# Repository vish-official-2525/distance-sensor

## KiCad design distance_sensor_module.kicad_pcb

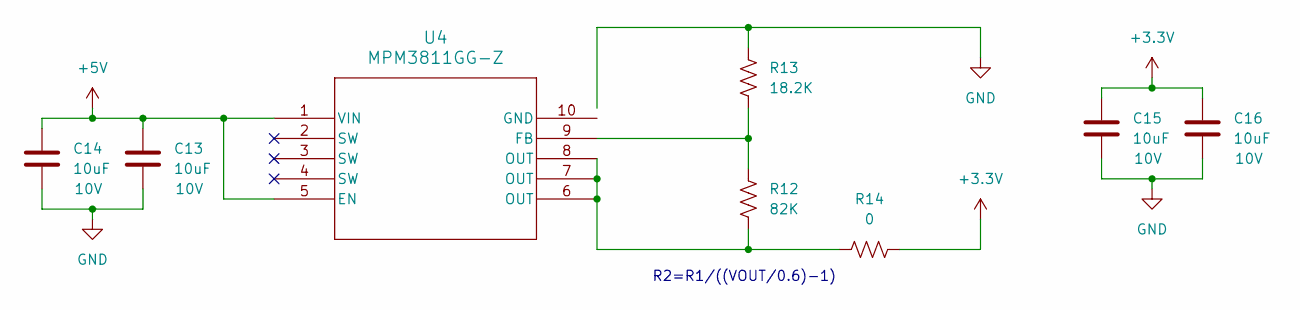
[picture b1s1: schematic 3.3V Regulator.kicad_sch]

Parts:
C13, C14, C15, C16: 10uF; C_0402_1005Metric_Pad0.74x0.62mm_HandSolder
R12: 82K; R_0402_1005Metric_Pad0.72x0.64mm_HandSolder
R13: 18.2K; R_0402_1005Metric_Pad0.72x0.64mm_HandSolder
R14: 0; R_0402_1005Metric_Pad0.72x0.64mm_HandSolder
U4: MPM3811GG-Z; QFN2x2x1p6_MPM3811_MNP

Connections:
+3.3V: C15.1, C16.1, R14.2; also elsewhere on the board
GND: C13.2, C14.2, C15.2, C16.2, R13.1; also elsewhere on the board
unnamed: R12.2, R14.1, U4.6 (OUT), U4.7 (OUT), U4.8 (OUT)
unnamed: R12.1, R13.2, U4.9 (FB)
VDDL: C13.1, C14.1, U4.1 (VIN), U4.5 (EN); also elsewhere on the board

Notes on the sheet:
R2=R1/((VOUT/0.6)-1)

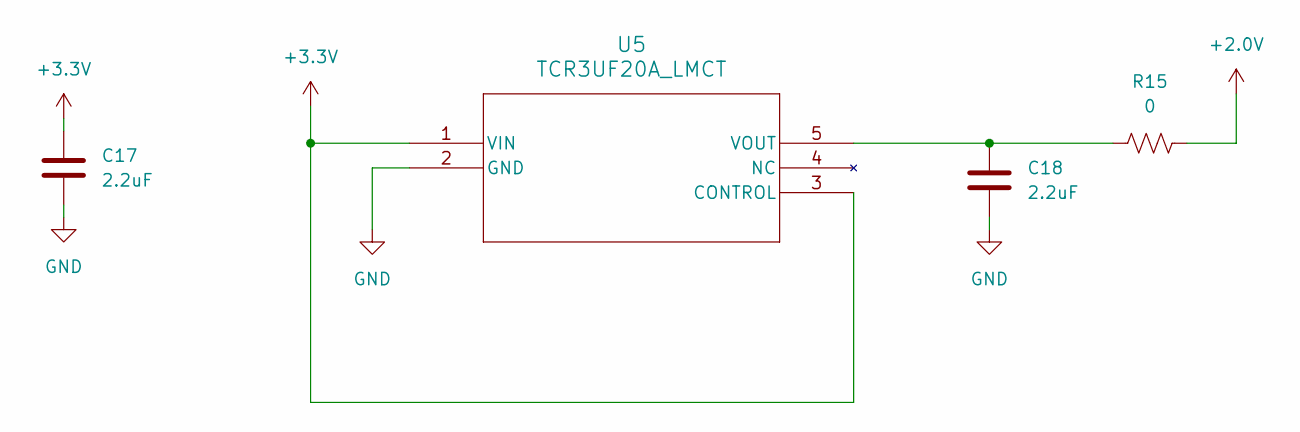
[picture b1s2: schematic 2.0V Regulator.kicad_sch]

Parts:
C17, C18: 2.2uF; C_0402_1005Metric_Pad0.74x0.62mm_HandSolder
R15: 0; R_0402_1005Metric_Pad0.72x0.64mm_HandSolder
U5: TCR3UF20A_LMCT; QFN2x2x1p6_MPM3811_MNP

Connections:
+2.0V: R15.2; also elsewhere on the board
+3.3V: C17.1, U5.1 (VIN), U5.3 (CONTROL); also elsewhere on the board
GND: C17.2, C18.2, U5.2 (GND); also elsewhere on the board
unnamed: C18.1, R15.1, U5.5 (VOUT)

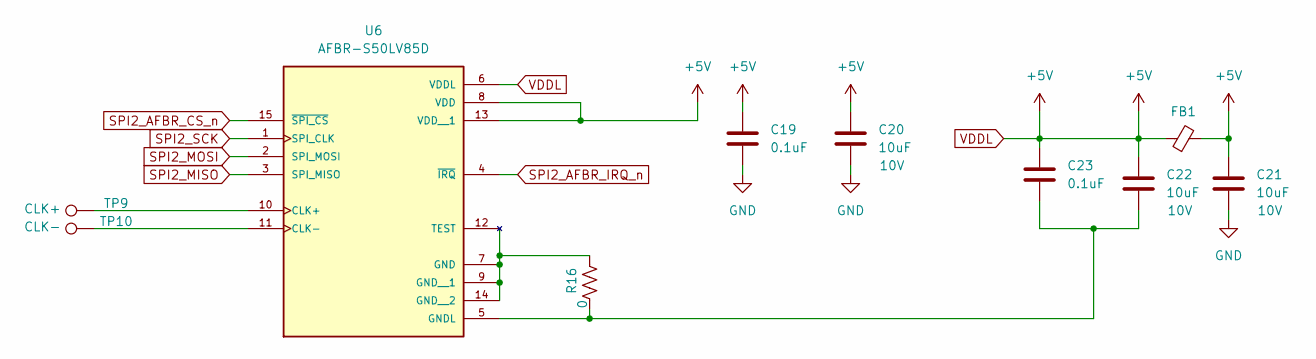
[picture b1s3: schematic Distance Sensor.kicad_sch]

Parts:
C19, C23: 0.1uF; C_0402_1005Metric_Pad0.74x0.62mm_HandSolder
C20, C21, C22: 10uF; C_0402_1005Metric_Pad0.74x0.62mm_HandSolder
FB1: FerriteBead_Small; L_0402_1005Metric_Pad0.77x0.64mm_HandSolder
R16: 0; R_0402_1005Metric_Pad0.72x0.64mm_HandSolder
TP9: CLK+; TestPoint_Pad_D1.0mm
TP10: CLK-; TestPoint_Pad_D1.0mm
U6: AFBR-S50LV85D; XCVR_AFBR-S50LV85D; PARTREV September 17, 2020

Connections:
GND: C19.2, C20.2, C21.2; also elsewhere on the board
unnamed: TP9.1, U6.10 (CLK+)
unnamed: TP10.1, U6.11 (CLK-)
unnamed: R16.2, U6.7 (GND), U6.9 (GND__1), U6.12 (TEST), U6.14 (GND__2)
unnamed: C22.2, C23.2, R16.1, U6.5 (GNDL)
SPI2_AFBR_CS_n: U6.15 (~SPI_CS); also elsewhere on the board
SPI2_AFBR_IRQ_n: U6.4 (~IRQ); also elsewhere on the board
SPI2_MISO: U6.3 (SPI_MISO); also elsewhere on the board
SPI2_MOSI: U6.2 (SPI_MOSI); also elsewhere on the board
SPI2_SCK: U6.1 (SPI_CLK); also elsewhere on the board
VDDL: C19.1, C20.1, C21.1, C22.1, C23.1, FB1.1, FB1.2, U6.6 (VDDL), U6.8 (VDD), U6.13 (VDD__1); also elsewhere on the board

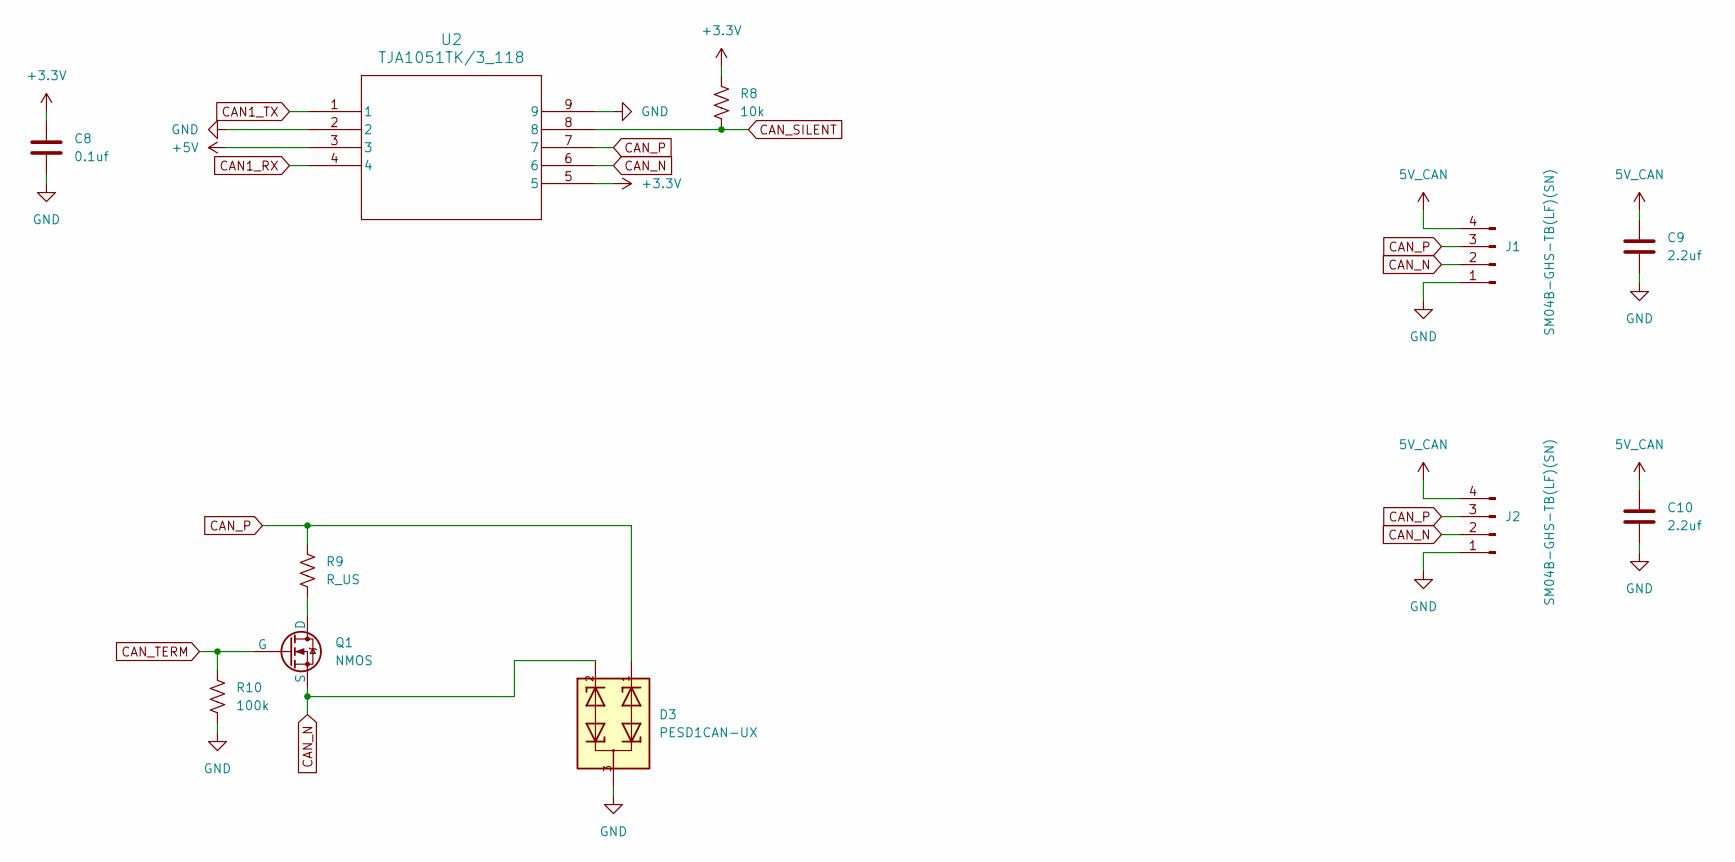
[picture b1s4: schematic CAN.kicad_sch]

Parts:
C8: 0.1uf; C_0402_1005Metric_Pad0.74x0.62mm_HandSolder
C9, C10: 2.2uf; C_0402_1005Metric_Pad0.74x0.62mm_HandSolder
D3: PESD1CAN-UX; SOT65P210X110-3N
J1, J2: SM04B-GHS-TB(LF)(SN); JST_GH_SM04B-GHS-TB_1x04-1MP_P1.25mm_Horizontal
Q1: NMOS; SOT91P240X110-3N
R8: 10k; R_0402_1005Metric_Pad0.72x0.64mm_HandSolder
R9: R_US; R_0402_1005Metric_Pad0.72x0.64mm_HandSolder
R10: 100k; R_0402_1005Metric_Pad0.72x0.64mm_HandSolder
U2: TJA1051TK/3_118; HVSON08_3X3_NXP

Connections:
5V_CAN: C9.1, C10.1, J1.4, J2.4; also elsewhere on the board
+3.3V: C8.1, R8.2, U2.5; also elsewhere on the board
CAN1_RX: U2.4; also elsewhere on the board
CAN1_TX: U2.1; also elsewhere on the board
CAN_N: D3.2, J1.2, J2.2, Q1.3 (S), U2.6
CAN_P: D3.1, J1.3, J2.3, R9.1, U2.7
CAN_SILENT: R8.1, U2.8; also elsewhere on the board
CAN_TERM: Q1.2 (G), R10.2; also elsewhere on the board
GND: C8.2, C9.2, C10.2, D3.3, J1.1, J2.1, R10.1, U2.2, U2.9; also elsewhere on the board
unnamed: Q1.1 (D), R9.2
VDDL: U2.3; also elsewhere on the board

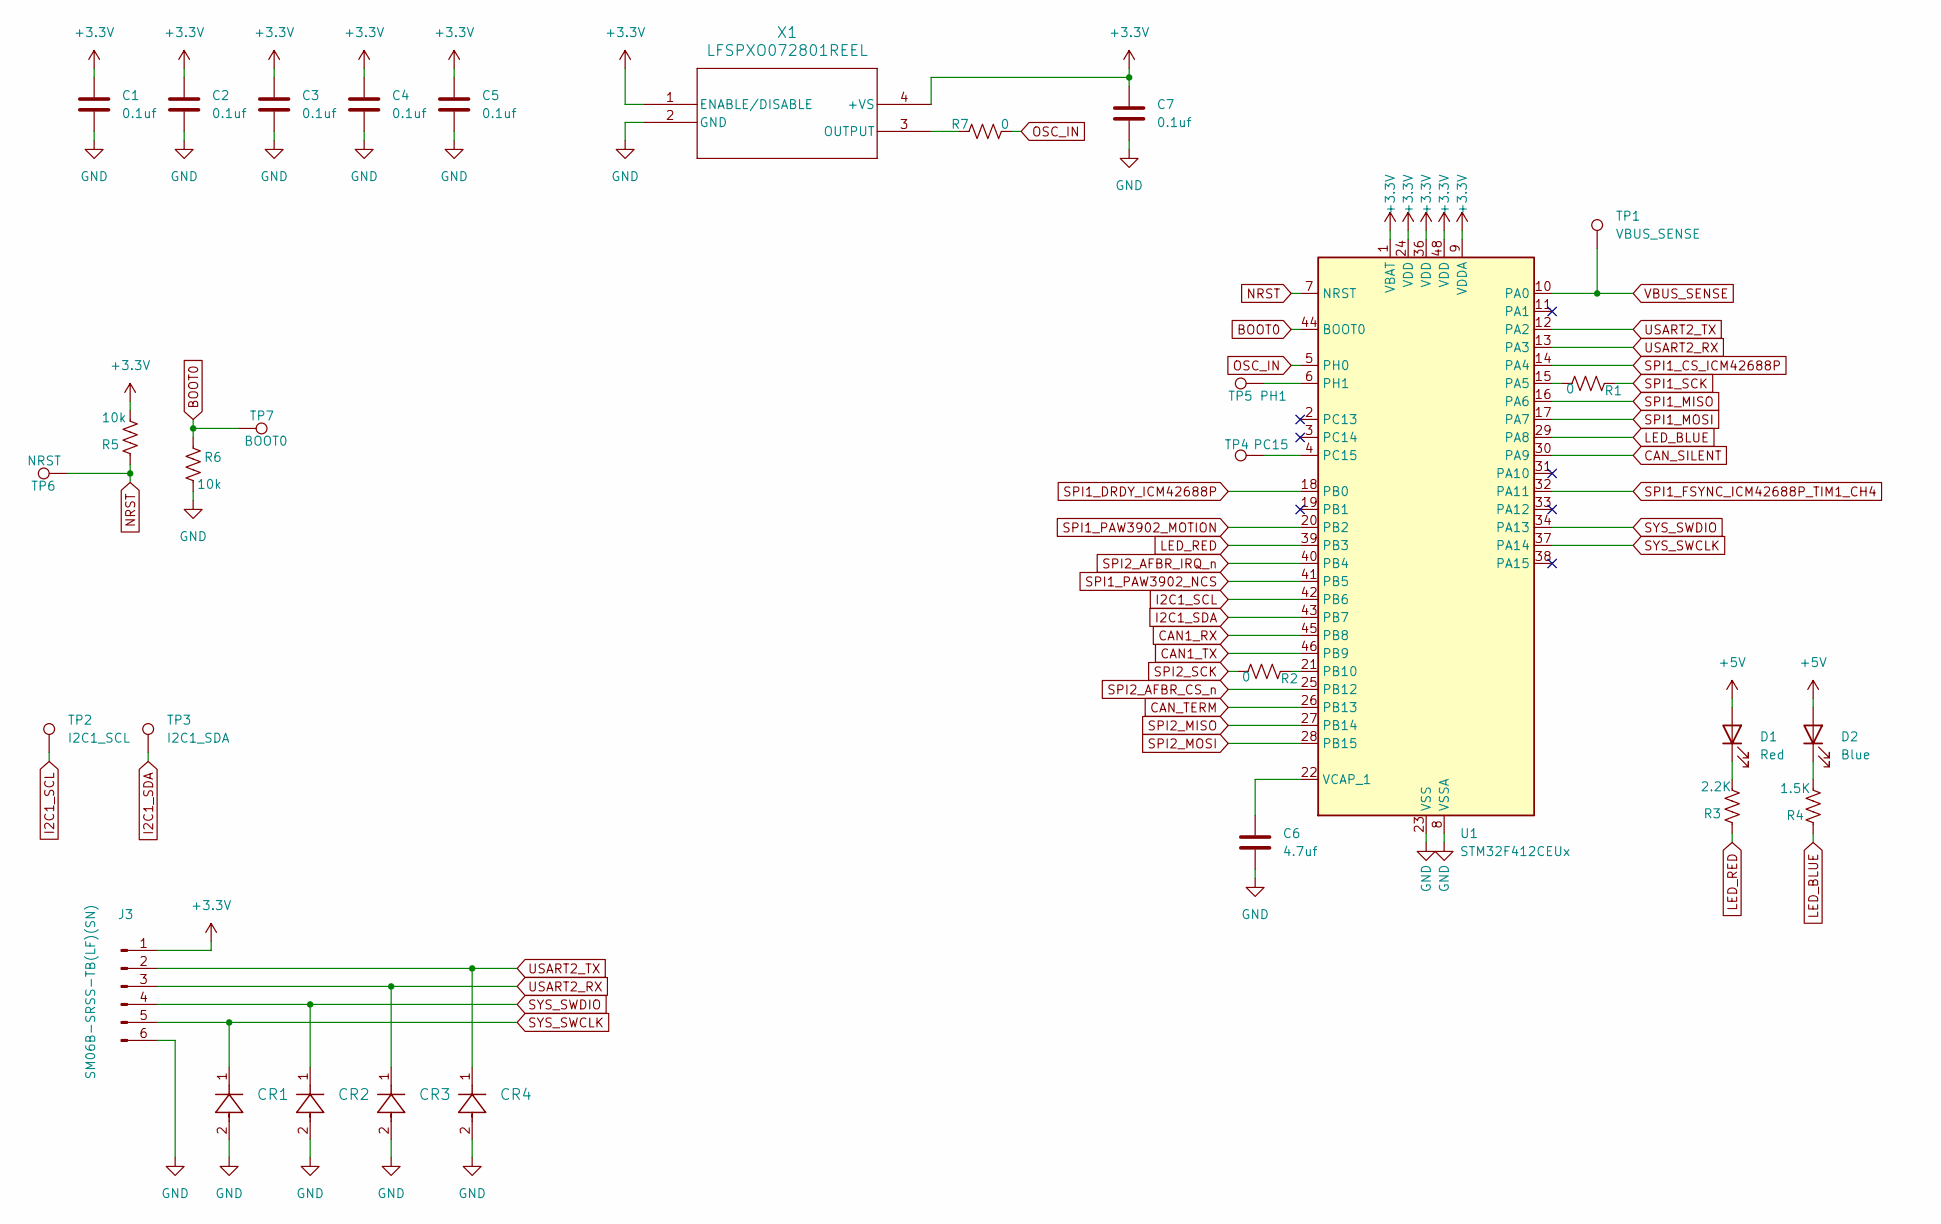
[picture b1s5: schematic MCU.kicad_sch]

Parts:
C1, C2, C3, C4, C5, C7: 0.1uf; C_0402_1005Metric_Pad0.74x0.62mm_HandSolder
C6: 4.7uf; C_0402_1005Metric_Pad0.74x0.62mm_HandSolder
CR1, CR2, CR3, CR4: ESD9C3.3ST5G; CR_ESD9C3.3ST5G_ONS
D1: Red; LED_0402_1005Metric_Pad0.77x0.64mm_HandSolder
D2: Blue; LED_0402_1005Metric_Pad0.77x0.64mm_HandSolder
J3: SM06B-SRSS-TB(LF)(SN); JST_SH_SM06B-SRSS-TB_1x06-1MP_P1.00mm_Horizontal
R1, R2, R7: 0; R_0402_1005Metric_Pad0.72x0.64mm_HandSolder
R3: 2.2K; R_0402_1005Metric_Pad0.72x0.64mm_HandSolder
R4: 1.5K; R_0402_1005Metric_Pad0.72x0.64mm_HandSolder
R5, R6: 10k; R_0402_1005Metric_Pad0.72x0.64mm_HandSolder
TP1: VBUS_SENSE; TestPoint_Pad_D1.0mm
TP2: I2C1_SCL; TestPoint_Pad_D1.0mm
TP3: I2C1_SDA; TestPoint_Pad_D1.0mm
TP4: PC15; TestPoint_Pad_D1.0mm
TP5: PH1; TestPoint_Pad_D1.0mm
TP6: NRST; TestPoint_Pad_D1.0mm
TP7: BOOT0; TestPoint_Pad_D1.0mm
U1: STM32F412CEUx; QFN-48-1EP_7x7mm_P0.5mm_EP3.5x3.5mm_ThermalVias
X1: LFSPXO072801REEL; LFSPXO072801REEL_IQD

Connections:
+3.3V: C1.1, C2.1, C3.1, C4.1, C5.1, C7.1, J3.1, R5.2, U1.1 (VBAT), U1.9 (VDDA), U1.24 (VDD), U1.36 (VDD), U1.48 (VDD), X1.1 (ENABLE/DISABLE), X1.4 (+VS); also elsewhere on the board
BOOT0: R6.1, TP7.1, U1.44 (BOOT0)
CAN1_RX: U1.45 (PB8); also elsewhere on the board
CAN1_TX: U1.46 (PB9); also elsewhere on the board
CAN_SILENT: U1.30 (PA9); also elsewhere on the board
CAN_TERM: U1.26 (PB13); also elsewhere on the board
GND: C1.2, C2.2, C3.2, C4.2, C5.2, C6.2, C7.2, CR1.2, CR2.2, CR3.2, CR4.2, J3.6, R6.2, U1.8 (VSSA), U1.23 (VSS), U1.35 (VSS), U1.47 (VSS), U1.49 (VSS), X1.2 (GND); also elsewhere on the board
I2C1_SCL: TP2.1, U1.42 (PB6)
I2C1_SDA: TP3.1, U1.43 (PB7)
LED_BLUE: R4.1, U1.29 (PA8)
LED_RED: R3.1, U1.39 (PB3)
NRST: R5.1, TP6.1, U1.7 (NRST)
unnamed: D1.1 (K), R3.2
unnamed: D2.1 (K), R4.2
unnamed: R1.1, U1.15 (PA5)
unnamed: R2.2, U1.21 (PB10)
unnamed: TP4.1, U1.4 (PC15)
unnamed: TP5.1, U1.6 (PH1)
unnamed: C6.1, U1.22 (VCAP_1)
unnamed: R7.1, X1.3 (OUTPUT)
OSC_IN: R7.2, U1.5 (PH0)
SPI1_CS_ICM42688P: U1.14 (PA4); also elsewhere on the board
SPI1_DRDY_ICM42688P: U1.18 (PB0); also elsewhere on the board
SPI1_FSYNC_ICM42688P_TIM1_CH4: U1.32 (PA11); also elsewhere on the board
SPI1_MISO: U1.16 (PA6); also elsewhere on the board
SPI1_MOSI: U1.17 (PA7); also elsewhere on the board
SPI1_PAW3902_MOTION: U1.20 (PB2); also elsewhere on the board
SPI1_PAW3902_NCS: U1.41 (PB5); also elsewhere on the board
SPI1_SCK: R1.2; also elsewhere on the board
SPI2_AFBR_CS_n: U1.25 (PB12); also elsewhere on the board
SPI2_AFBR_IRQ_n: U1.40 (PB4); also elsewhere on the board
SPI2_MISO: U1.27 (PB14); also elsewhere on the board
SPI2_MOSI: U1.28 (PB15); also elsewhere on the board
SPI2_SCK: R2.1; also elsewhere on the board
SYS_SWCLK: CR1.1, J3.5, U1.37 (PA14)
SYS_SWDIO: CR2.1, J3.4, U1.34 (PA13)
USART2_RX: CR3.1, J3.3, U1.13 (PA3)
USART2_TX: CR4.1, J3.2, U1.12 (PA2)
VBUS_SENSE: TP1.1, U1.10 (PA0)
VDDL: D1.2 (A), D2.2 (A); also elsewhere on the board

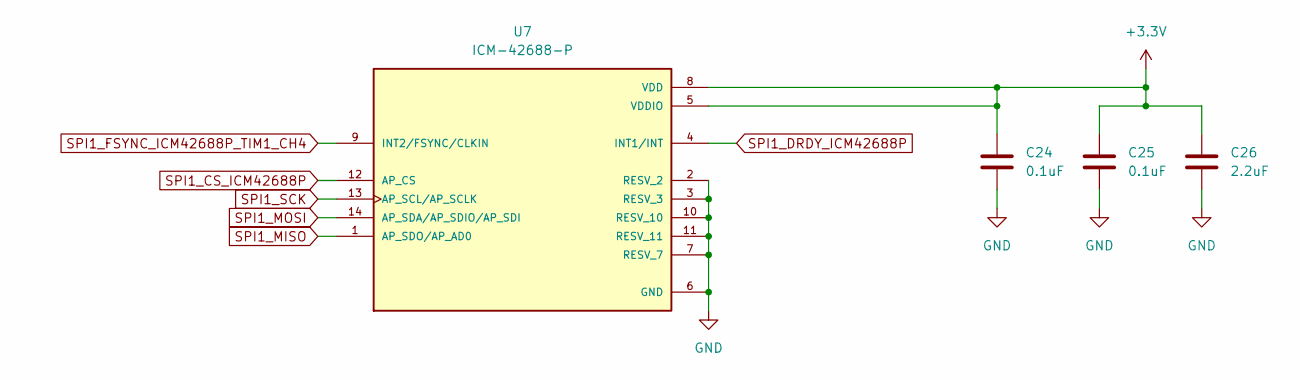
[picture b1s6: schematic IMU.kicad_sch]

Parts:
C24, C25: 0.1uF; C_0402_1005Metric_Pad0.74x0.62mm_HandSolder
C26: 2.2uF; C_0402_1005Metric_Pad0.74x0.62mm_HandSolder
U7: ICM-42688-P; PQFN50P300X250X97-14N; PARTREV 1.2

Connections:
+3.3V: C24.1, C25.1, C26.1, U7.5 (VDDIO), U7.8 (VDD); also elsewhere on the board
GND: C24.2, C25.2, C26.2, U7.2 (RESV_2), U7.3 (RESV_3), U7.6 (GND), U7.7 (RESV_7), U7.10 (RESV_10), U7.11 (RESV_11); also elsewhere on the board
SPI1_CS_ICM42688P: U7.12 (AP_CS); also elsewhere on the board
SPI1_DRDY_ICM42688P: U7.4 (INT1/INT); also elsewhere on the board
SPI1_FSYNC_ICM42688P_TIM1_CH4: U7.9 (INT2/FSYNC/CLKIN); also elsewhere on the board
SPI1_MISO: U7.1 (AP_SDO/AP_AD0); also elsewhere on the board
SPI1_MOSI: U7.14 (AP_SDA/AP_SDIO/AP_SDI); also elsewhere on the board
SPI1_SCK: U7.13 (AP_SCL/AP_SCLK); also elsewhere on the board

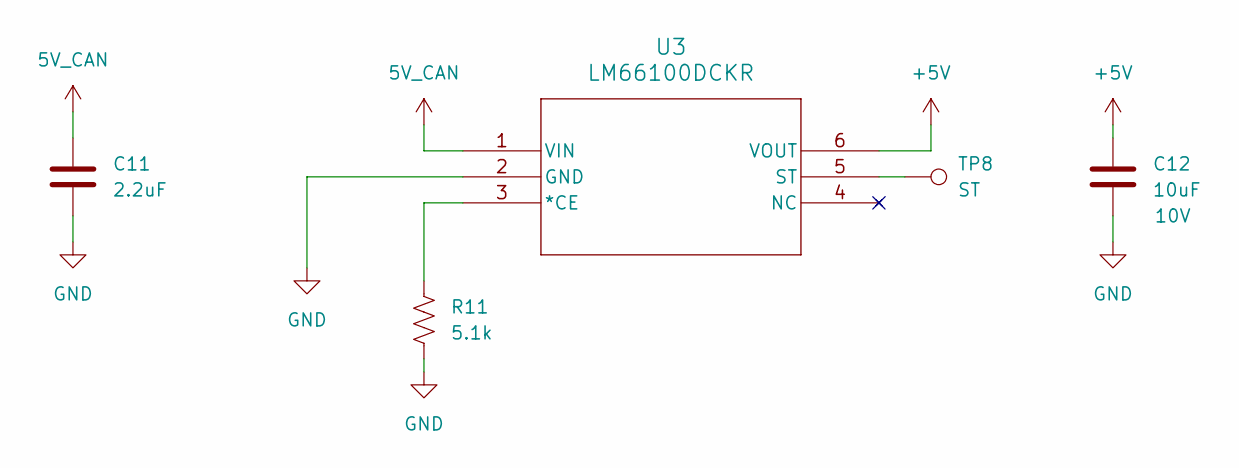
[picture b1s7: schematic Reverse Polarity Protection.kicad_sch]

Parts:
C11: 2.2uF; C_0402_1005Metric_Pad0.74x0.62mm_HandSolder
C12: 10uF; C_0402_1005Metric_Pad0.74x0.62mm_HandSolder
R11: 5.1k; R_0402_1005Metric_Pad0.72x0.64mm_HandSolder
TP8: ST; TestPoint_Pad_D1.0mm
U3: LM66100DCKR; DCK6_TEX

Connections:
5V_CAN: C11.1, U3.1 (VIN); also elsewhere on the board
GND: C11.2, C12.2, R11.2, U3.2 (GND); also elsewhere on the board
unnamed: R11.1, U3.3 (*CE)
unnamed: TP8.1, U3.5 (ST)
VDDL: C12.1, U3.6 (VOUT); also elsewhere on the board

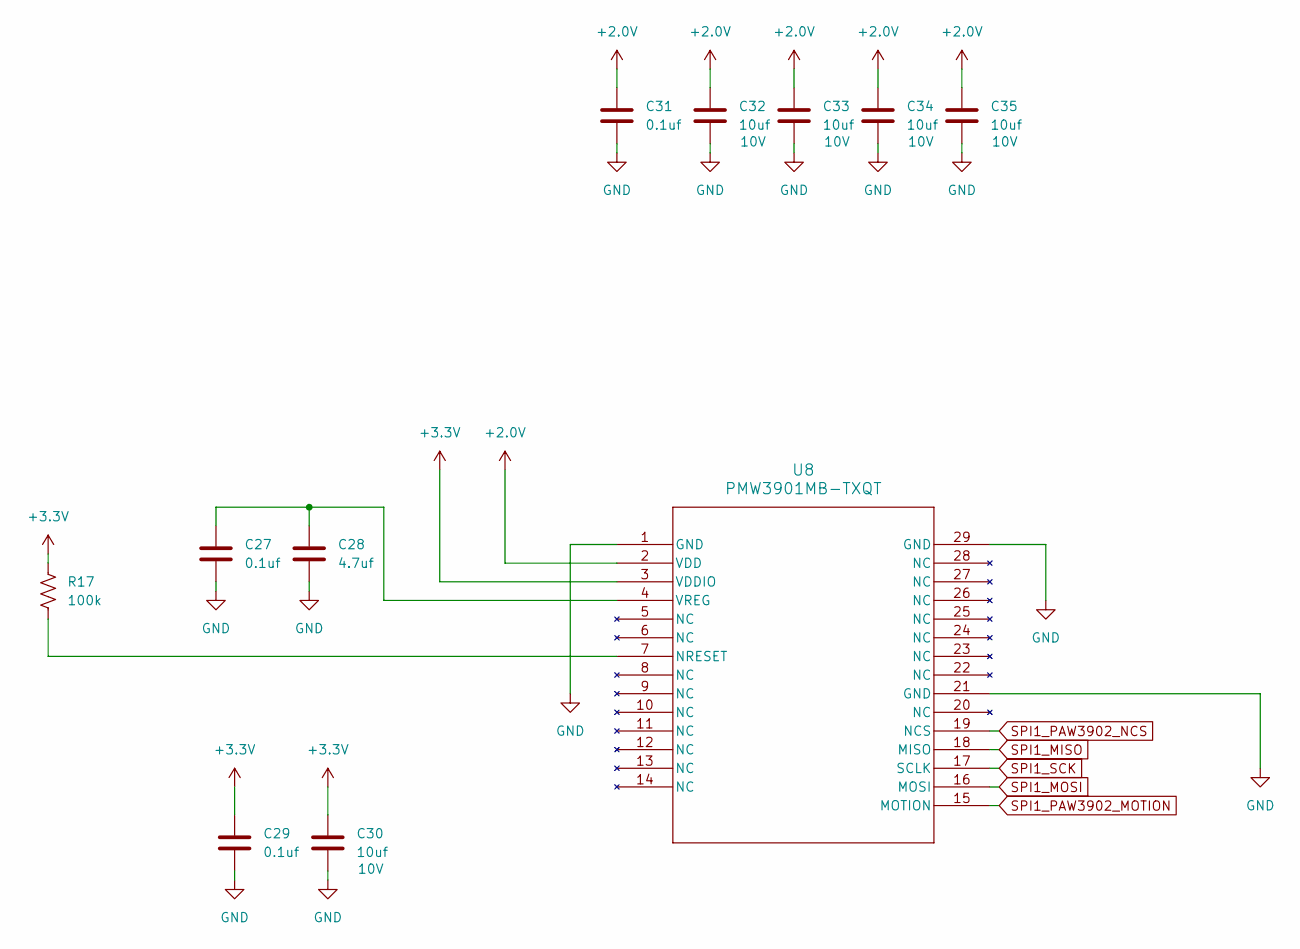
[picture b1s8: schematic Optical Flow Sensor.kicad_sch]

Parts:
C27, C29, C31: 0.1uf; C_0402_1005Metric_Pad0.74x0.62mm_HandSolder
C28: 4.7uf; C_0402_1005Metric_Pad0.74x0.62mm_HandSolder
C30, C32, C33, C34, C35: 10uf; C_0402_1005Metric_Pad0.74x0.62mm_HandSolder
R17: 100k; R_0402_1005Metric_Pad0.72x0.64mm_HandSolder
U8: PMW3901MB-TXQT; QFN_01MB-TXQT_PIX-M

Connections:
+2.0V: C31.1, C32.1, C33.1, C34.1, C35.1, U8.2 (VDD); also elsewhere on the board
+3.3V: C29.1, C30.1, R17.1, U8.3 (VDDIO); also elsewhere on the board
GND: C27.2, C28.2, C29.2, C30.2, C31.2, C32.2, C33.2, C34.2, C35.2, U8.1 (GND), U8.21 (GND), U8.29 (GND); also elsewhere on the board
unnamed: R17.2, U8.7 (NRESET)
unnamed: C27.1, C28.1, U8.4 (VREG)
SPI1_MISO: U8.18 (MISO); also elsewhere on the board
SPI1_MOSI: U8.16 (MOSI); also elsewhere on the board
SPI1_PAW3902_MOTION: U8.15 (MOTION); also elsewhere on the board
SPI1_PAW3902_NCS: U8.19 (NCS); also elsewhere on the board
SPI1_SCK: U8.17 (SCLK); also elsewhere on the board

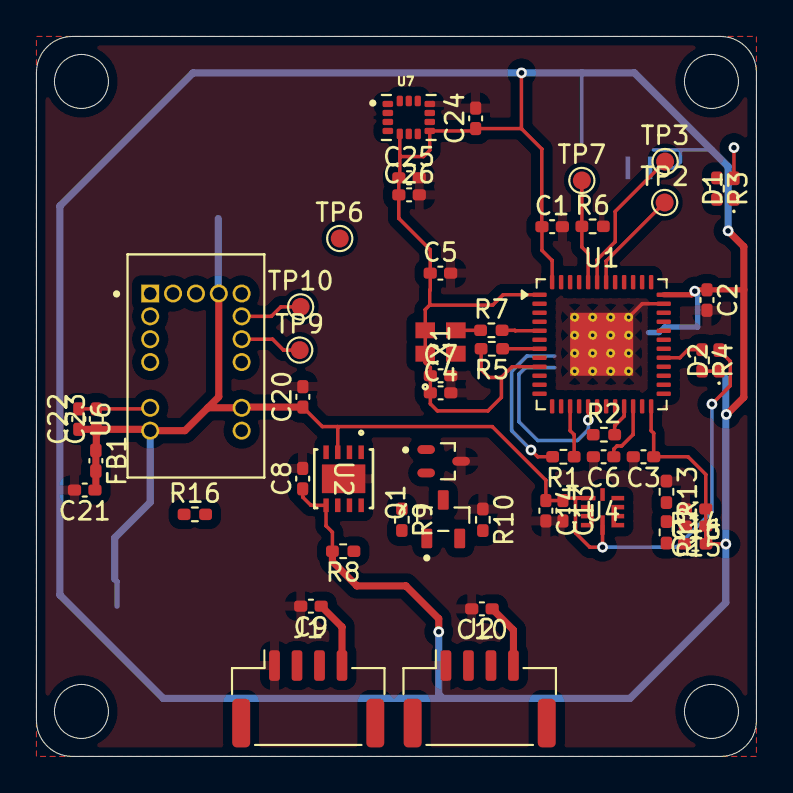
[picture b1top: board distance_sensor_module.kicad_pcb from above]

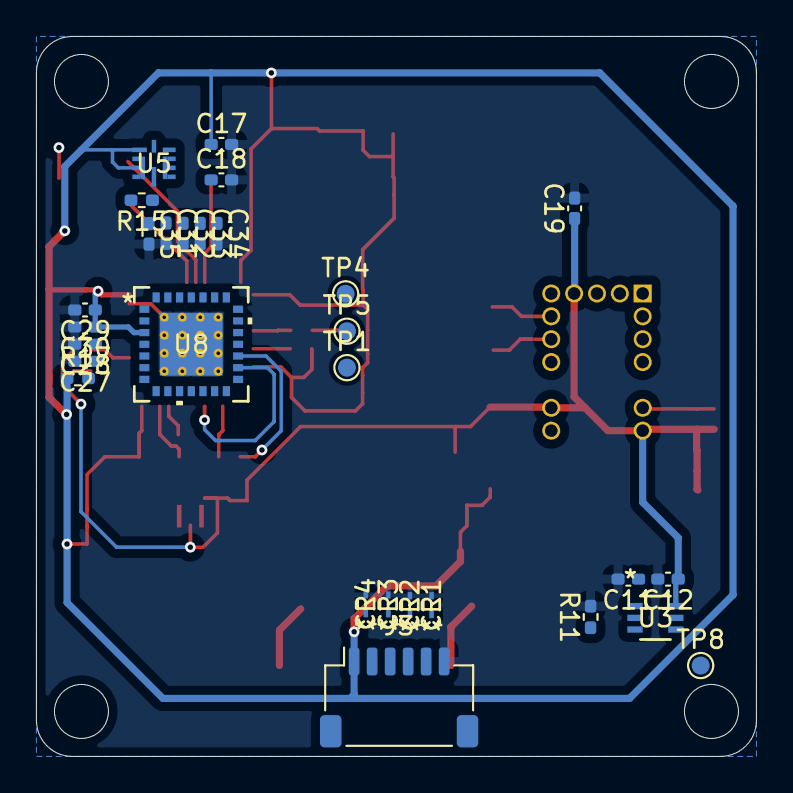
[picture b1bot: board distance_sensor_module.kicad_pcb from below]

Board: 4 copper layers, 40.0 x 40.0 mm, 83 parts (29 on the bottom side), 56 nets.

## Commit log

2025-12-27 distance sensor
